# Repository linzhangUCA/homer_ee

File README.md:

# homer_ee

Electrical and electronic designs for HomeR

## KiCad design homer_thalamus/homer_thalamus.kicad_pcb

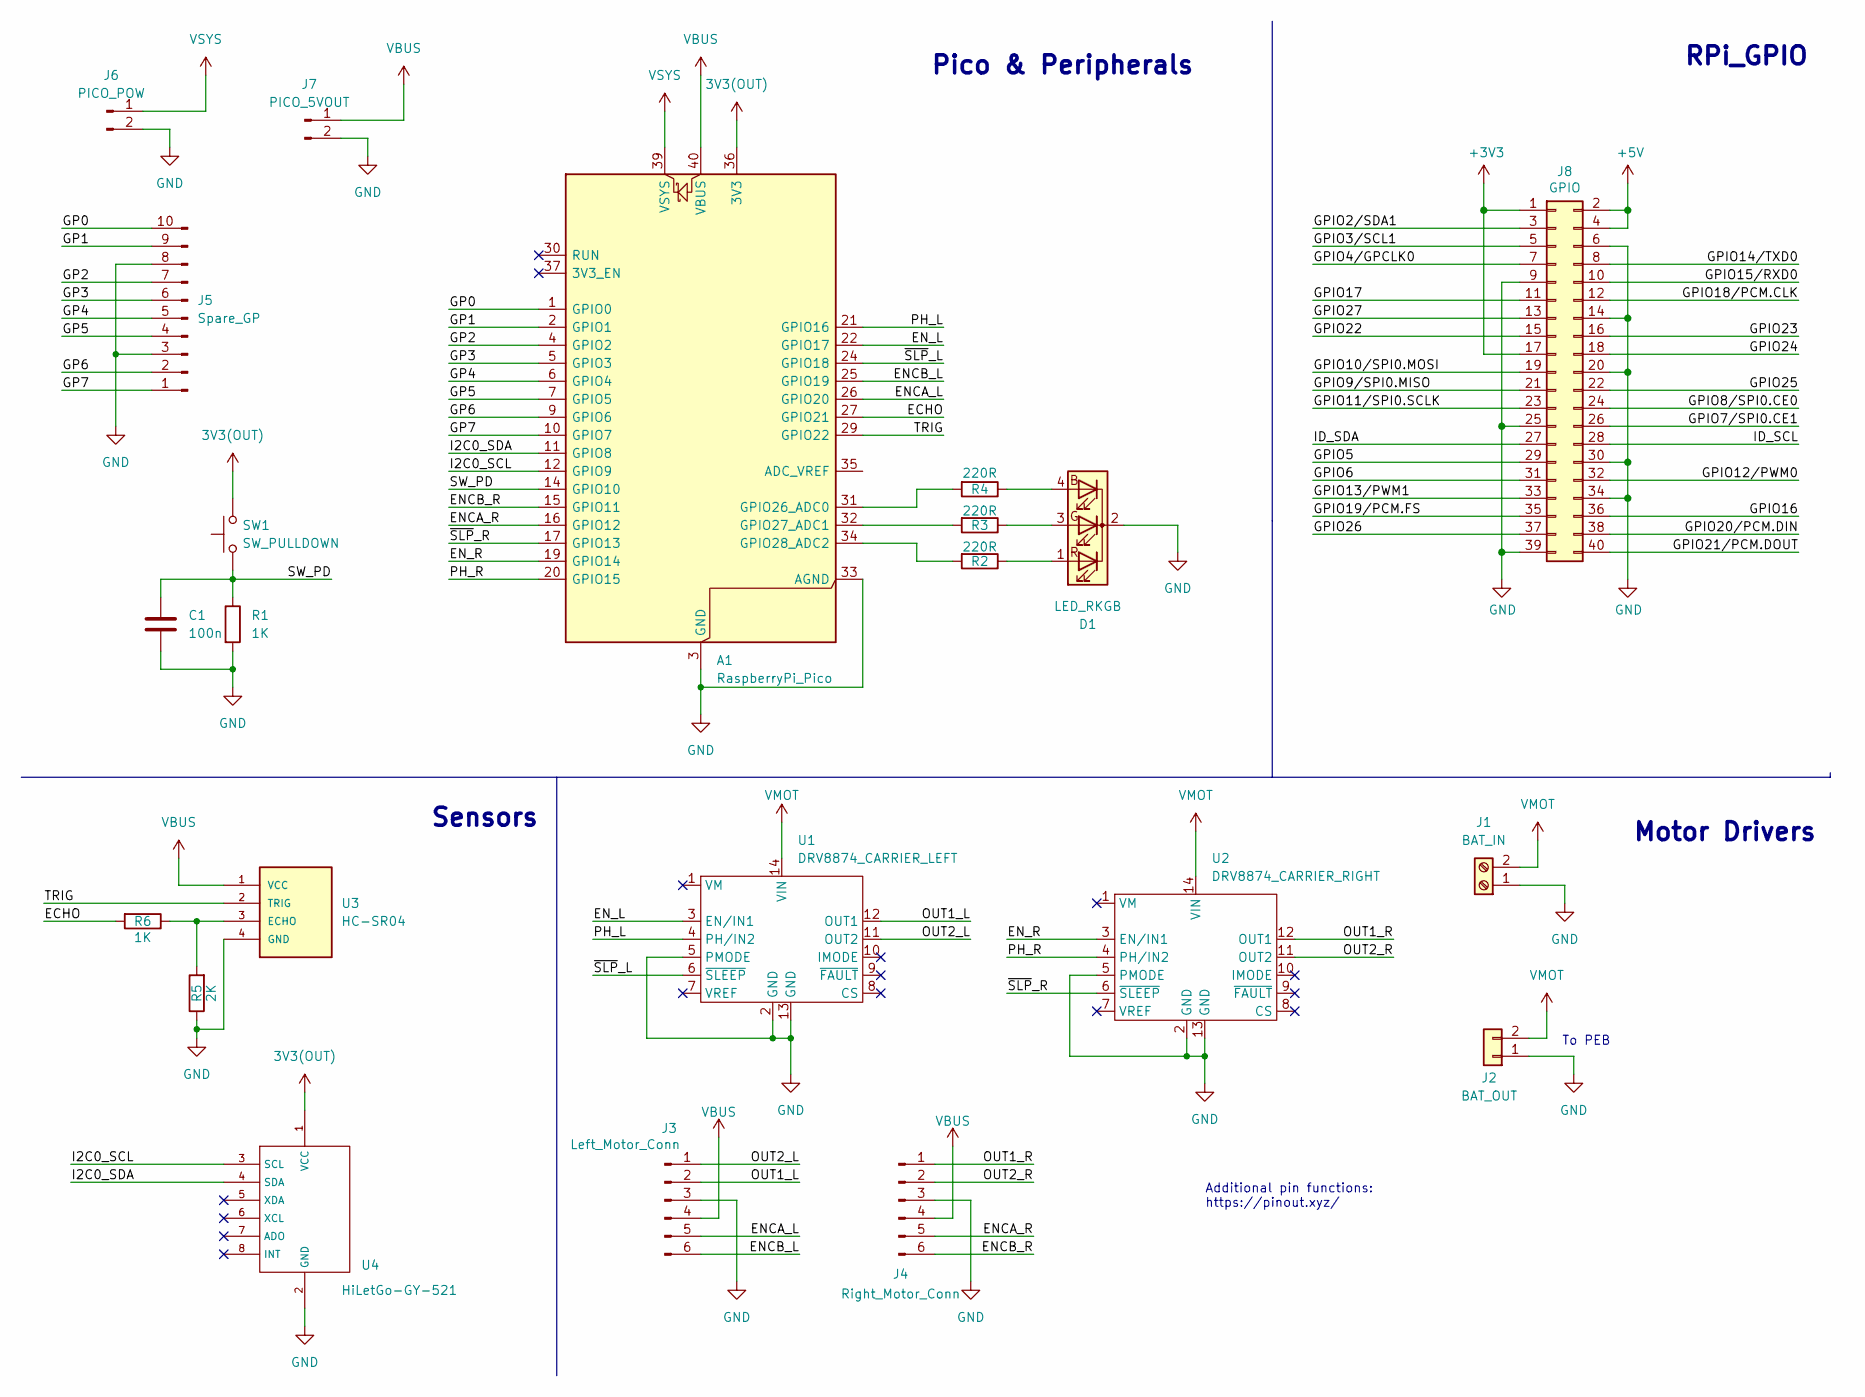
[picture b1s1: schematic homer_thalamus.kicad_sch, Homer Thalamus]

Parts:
A1: RaspberryPi_Pico; RaspberryPi_Pico_THT
C1: 100n; C_Disc_D4.7mm_W2.5mm_P5.00mm
D1: LED_RKGB; LED_D5.0mm-4_RGB_Wide_Pins
J1: BAT_IN; TerminalBlock_MaiXu_MX126-5.0-02P_1x02_P5.00mm
J2: BAT_OUT; JST_XH_B2B-XH-A_1x02_P2.50mm_Vertical
J3: Left_Motor_Conn; PinHeader_1x06_P2.54mm_Vertical
J4: Right_Motor_Conn; PinHeader_1x06_P2.54mm_Vertical
J5: Spare_GP; PinHeader_1x10_P2.54mm_Vertical
J6: PICO_POW; PinHeader_1x02_P2.54mm_Horizontal
J7: PICO_5VOUT; PinHeader_1x02_P2.54mm_Vertical
J8: GPIO; PinSocket_2x20_P2.54mm_Vertical
R1, R6: 1K; R_Axial_DIN0207_L6.3mm_D2.5mm_P7.62mm_Horizontal
R2, R3, R4: 220R; R_Axial_DIN0207_L6.3mm_D2.5mm_P7.62mm_Horizontal
R5: 2K; R_Axial_DIN0207_L6.3mm_D2.5mm_P7.62mm_Horizontal
SW1: SW_PULLDOWN; SW_PUSH_6mm
U1: DRV8874_CARRIER_LEFT; DRV8874_Carrier
U2: DRV8874_CARRIER_RIGHT; DRV8874_Carrier
U3: HC-SR04; XCVR_HC-SR04
U4: HiLetGo-GY-521

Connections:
3V3(OUT): A1.36 (3V3), SW1.2, U4.1 (VCC)
+3V3: J8.1, J8.17
+5V: J8.2, J8.4
/ECHO: A1.27 (GPIO21), R6.2
/ENCA_L: A1.26 (GPIO20), J3.5
/ENCA_R: A1.16 (GPIO12), J4.5
/ENCB_L: A1.25 (GPIO19), J3.6
/ENCB_R: A1.15 (GPIO11), J4.6
/EN_L: A1.22 (GPIO17), U1.3 (EN/IN1)
/EN_R: A1.19 (GPIO14), U2.3 (EN/IN1)
/GP0: A1.1 (GPIO0), J5.10
/GP1: A1.2 (GPIO1), J5.9
/GP2: A1.4 (GPIO2), J5.7
/GP3: A1.5 (GPIO3), J5.6
/GP4: A1.6 (GPIO4), J5.5
/GP5: A1.7 (GPIO5), J5.4
/GP6: A1.9 (GPIO6), J5.2
/GP7: A1.10 (GPIO7), J5.1
/GPIO2/SDA1: J8.3
/GPIO3/SCL1: J8.5
/GPIO4/GPCLK0: J8.7
/GPIO5: J8.29
/GPIO6: J8.31
/GPIO7/SPI0.CE1: J8.26
/GPIO8/SPI0.CE0: J8.24
/GPIO9/SPI0.MISO: J8.21
/GPIO10/SPI0.MOSI: J8.19
/GPIO11/SPI0.SCLK: J8.23
/GPIO12/PWM0: J8.32
/GPIO13/PWM1: J8.33
/GPIO14/TXD0: J8.8
/GPIO15/RXD0: J8.10
/GPIO16: J8.36
/GPIO17: J8.11
/GPIO18/PCM.CLK: J8.12
/GPIO19/PCM.FS: J8.35
/GPIO20/PCM.DIN: J8.38
/GPIO21/PCM.DOUT: J8.40
/GPIO22: J8.15
/GPIO23: J8.16
/GPIO24: J8.18
/GPIO25: J8.22
/GPIO26: J8.37
/GPIO27: J8.13
/I2C0_SCL: A1.12 (GPIO9), U4.3 (SCL)
/I2C0_SDA: A1.11 (GPIO8), U4.4 (SDA)
/ID_SCL: J8.28
/ID_SDA: J8.27
/OUT1_L: J3.2, U1.12 (OUT1)
/OUT1_R: J4.1, U2.12 (OUT1)
/OUT2_L: J3.1, U1.11 (OUT2)
/OUT2_R: J4.2, U2.11 (OUT2)
/PH_L: A1.21 (GPIO16), U1.4 (PH/IN2)
/PH_R: A1.20 (GPIO15), U2.4 (PH/IN2)
/SW_PD: A1.14 (GPIO10), C1.1, R1.1, SW1.1
/TRIG: A1.29 (GPIO22), U3.2 (TRIG)
/~SLP_L: A1.24 (GPIO18), U1.6 (~SLEEP)
/~SLP_R: A1.17 (GPIO13), U2.6 (~SLEEP)
GND: A1.3 (GND), A1.8 (GND), A1.13 (GND), A1.18 (GND), A1.23 (GND), A1.28 (GND), A1.33 (AGND), A1.38 (GND), C1.2, D1.2 (K), J1.1, J2.1, J3.3, J4.3, J5.3, J5.8, J6.2, J7.2, J8.6, J8.9, J8.14, J8.20, J8.25, J8.30, J8.34, J8.39, R1.2, R5.1, U1.2 (GND), U1.5 (PMODE), U1.13 (GND), U2.2 (GND), U2.5 (PMODE), U2.13 (GND), U3.4 (GND), U4.2 (GND)
unnamed: A1.31 (GPIO26_ADC0), R4.2
unnamed: A1.32 (GPIO27_ADC1), R3.2
unnamed: A1.34 (GPIO28_ADC2), R2.2
unnamed: D1.4 (BA), R4.1
unnamed: D1.3 (GA), R3.1
unnamed: D1.1 (RA), R2.1
unnamed: R5.2, R6.1, U3.3 (ECHO)
VBUS: A1.40 (VBUS), J3.4, J4.4, J7.1, U3.1 (VCC)
VMOT: J1.2, J2.2, U1.14 (VIN), U2.14 (VIN)
VSYS: A1.39 (VSYS), J6.1

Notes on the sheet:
Motor Drivers
Pico & Peripherals
Additional pin functions: https://pinout.xyz/
To PEB
RPi_GPIO
Sensors

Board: 4 copper layers, 26 parts (2 on the bottom side), 41 nets, no tracks yet.

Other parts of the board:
MH1, MH2, MH3, MH4: MountingHole_2.7mm_M2.5

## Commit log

2025-12-04 init kicad project
2025-12-05 create drv8874 symbol
2025-12-17 update carrier board pin types
2025-12-19 change VM to power output pin
2025-12-19 start drv8874 carrier footprint
2025-12-20 update drv8874 carrier's footprint
2025-12-20 add peripherals
    - Button
    - RGB LED
    - HC-SR04
2025-12-20 update motor driving and sensing section
2025-12-20 add gy-521 resources
2025-12-20 add gy-521 to schematic
2025-12-20 finish up schematic v0
2025-12-20 assign footprints
2025-12-20 update pcb setup and edge cut
2025-12-20 update pcb layout
2025-12-21 update layout
2025-12-21 update motor connector position
2025-12-22 update GY521 symbol and footprint
2025-12-22 update drv8874 carrier footprint
2025-12-22 update pico footprint
2025-12-22 route pcb tracks
2025-12-22 add GY521 mounting and 3d model
2025-12-22 add 3d models to motor drivers and HC-SR04
2025-12-22 create gerbers
2025-12-22 export schematic
2025-12-22 final save
2025-12-22 add schematic to readme
2026-02-01 minor update pcb labels and new gerber
2026-02-13 start optimize schematic
2026-02-13 reorganize sch
2026-02-13 update footprints
2026-02-14 pcb layout in progress
2026-02-15 in progress, pcb layout
